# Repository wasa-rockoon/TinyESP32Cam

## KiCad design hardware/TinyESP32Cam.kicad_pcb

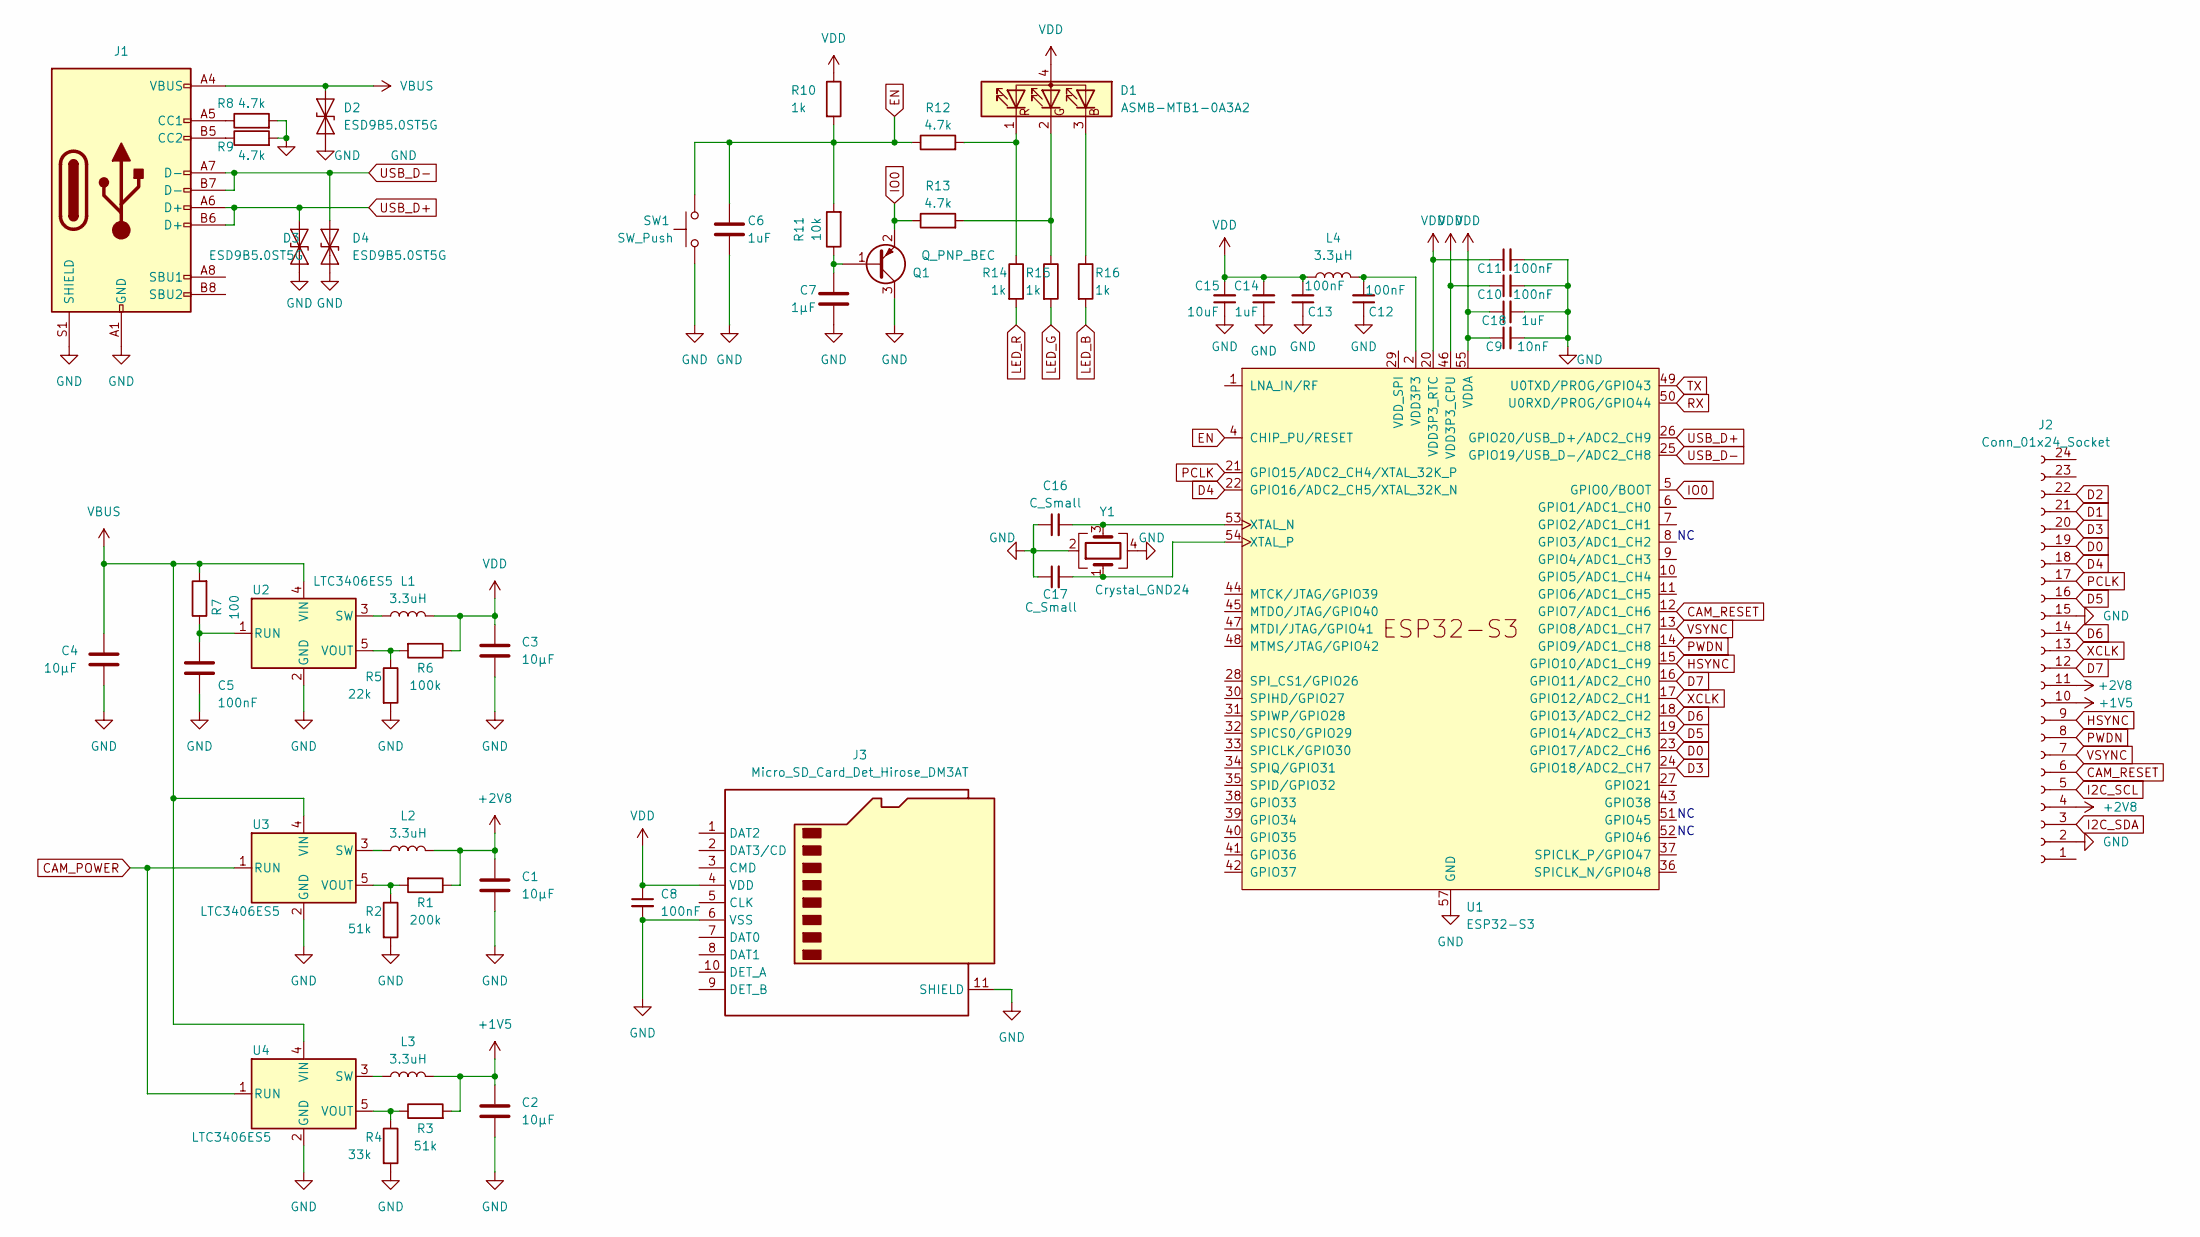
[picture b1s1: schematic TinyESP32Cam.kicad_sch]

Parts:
C1, C2, C3, C4: 10µF; C_0603_1608Metric
C5, C8, C10, C11, C12, C13: 100nF; C_0402_1005Metric
C6, C14, C18: 1uF; C_0402_1005Metric
C7: 1µF; C_0402_1005Metric
C9: 10nF; C_0402_1005Metric
C15: 10uF; C_0603_1608Metric
C16, C17: C_Small; C_0402_1005Metric
D1: ASMB-MTB1-0A3A2; LED_Cree-PLCC4_2x2mm_CW
D2, D3, D4: ESD9B5.0ST5G; D_SOD-523
J1: TYPE-C 16PFS 2JCB0.8-H7.45 IPX8; USB-C-SMD_SHOUHAN_TYPE-C-16PFS-2JCB0.8-H7.45
J2: Conn_01x24_Socket; Hirose_FH12-24S-0.5SH_1x24-1MP_P0.50mm_Horizontal
J3: Micro_SD_Card_Det_Hirose_DM3AT; microSD_HC_Hirose_DM3AT-SF-PEJM5
L1, L2, L3: 3.3uH; L_Murata_LQH2MCNxxxx02_2.0x1.6mm
L4: 3.3µH; L_Murata_LQH2MCNxxxx02_2.0x1.6mm
Q1: Q_PNP_BEC; SOT-23
R1: 200k; R_0402_1005Metric
R2, R3: 51k; R_0402_1005Metric
R4: 33k; R_0402_1005Metric
R5: 22k; R_0402_1005Metric
R6: 100k; R_0402_1005Metric
R7: 100; R_0402_1005Metric
R8, R9, R12, R13: 4.7k; R_0402_1005Metric
R10, R14, R15, R16: 1k; R_0402_1005Metric
R11: 10k; R_0402_1005Metric
SW1: SW_Push; SW_SPST_CK_KXT3
U1: ESP32-S3; QFN-56-1EP_7x7mm_P0.4mm_EP5.6x5.6mm
U2, U3, U4: LTC3406ES5; TSOT-23-5
Y1: Crystal_GND24; Crystal_SMD_2520-4Pin_2.5x2.0mm

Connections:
+1V5: C2.1, J2.10, L3.2, R3.2
+2V8: C1.1, J2.4, J2.11, L2.2, R1.1
CAM_POWER: U3.1 (RUN), U4.1 (RUN)
CAM_RESET: J2.6, U1.12 (GPIO7/ADC1_CH6)
D0: J2.19, U1.23 (GPIO17/ADC2_CH6)
D1: J2.21
D2: J2.22
D3: J2.20, U1.24 (GPIO18/ADC2_CH7)
D4: J2.18, U1.22 (GPIO16/ADC2_CH5/XTAL_32K_N)
D5: J2.16, U1.19 (GPIO14/ADC2_CH3)
D6: J2.14, U1.18 (GPIO13/ADC2_CH2)
D7: J2.12, U1.16 (GPIO11/ADC2_CH0)
EN: C6.1, R10.2, R11.2, R12.1, SW1.2, U1.4 (CHIP_PU/RESET)
GND: C1.2, C2.2, C3.2, C4.2, C5.2, C6.2, C7.2, C8.2, C9.2, C10.2, C11.2, C12.1, C13.1, C14.1, C15.1, C16.1, C17.1, C18.2, D2.1 (A1), D3.1 (A1), D4.1 (A1), J1.A1 (GND), J1.A12 (GND), J1.B1 (GND), J1.B12 (GND), J1.S1 (SHIELD), J2.2, J2.15, J3.6 (VSS), J3.11 (SHIELD), Q1.3 (C), R2.2, R4.2, R5.2, R8.2, R9.2, SW1.1, U1.57 (GND), U2.2 (GND), U3.2 (GND), U4.2 (GND), Y1.2, Y1.4
HSYNC: J2.9, U1.15 (GPIO10/ADC1_CH9)
I2C_SCL: J2.5
I2C_SDA: J2.3
IO0: Q1.2 (E), R13.1, U1.5 (GPIO0/BOOT)
LED_B: R16.2
LED_G: R15.2
LED_R: R14.2
unnamed: D1.3 (BK), R16.1
unnamed: D1.2 (GK), R13.2, R15.1
unnamed: D1.1 (RK), R12.2, R14.1
unnamed: J1.A5 (CC1), R8.1
unnamed: J1.B5 (CC2), R9.1
unnamed: C7.1, Q1.1 (B), R11.1
unnamed: C16.2, U1.53 (XTAL_N), Y1.3
unnamed: C17.2, U1.54 (XTAL_P), Y1.1
unnamed: C5.1, R7.1, U2.1 (RUN)
unnamed: L1.1, U2.3 (SW)
unnamed: R5.1, R6.2, U2.5 (VOUT)
unnamed: L2.1, U3.3 (SW)
unnamed: R1.2, R2.1, U3.5 (VOUT)
unnamed: L3.1, U4.3 (SW)
unnamed: R3.1, R4.1, U4.5 (VOUT)
PCLK: J2.17, U1.21 (GPIO15/ADC2_CH4/XTAL_32K_P)
PWDN: J2.8, U1.14 (GPIO9/ADC1_CH8)
RX: U1.50 (U0RXD/PROG/GPIO44)
TX: U1.49 (U0TXD/PROG/GPIO43)
USB_D+: D3.2 (A2), J1.A6 (D+), J1.B6 (D+), U1.26 (GPIO20/USB_D+/ADC2_CH9)
USB_D-: D4.2 (A2), J1.A7 (D-), J1.B7 (D-), U1.25 (GPIO19/USB_D-/ADC2_CH8)
VBUS: C4.1, D2.2 (A2), J1.A4 (VBUS), J1.A9 (VBUS), J1.B4 (VBUS), J1.B9 (VBUS), R7.2, U2.4 (VIN), U3.4 (VIN), U4.4 (VIN)
VDD: C3.1, C8.1, C9.1, C10.1, C11.1, C13.2, C14.2, C15.2, C18.1, D1.4 (A), J3.4 (VDD), L1.2, L4.1, R6.1, R10.1, U1.20 (VDD3P3_RTC), U1.46 (VDD3P3_CPU), U1.55 (VDDA), U1.56 (VDDA)
VDD3P3: C12.2, L4.2, U1.2 (VDD3P3), U1.3 (VDD3P3)
VSYNC: J2.7, U1.13 (GPIO8/ADC1_CH7)
XCLK: J2.13, U1.17 (GPIO12/ADC2_CH1)

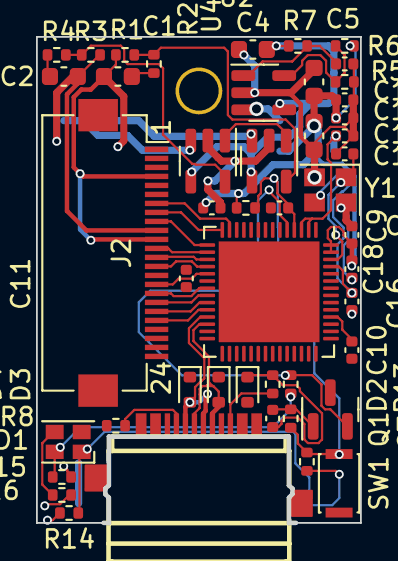
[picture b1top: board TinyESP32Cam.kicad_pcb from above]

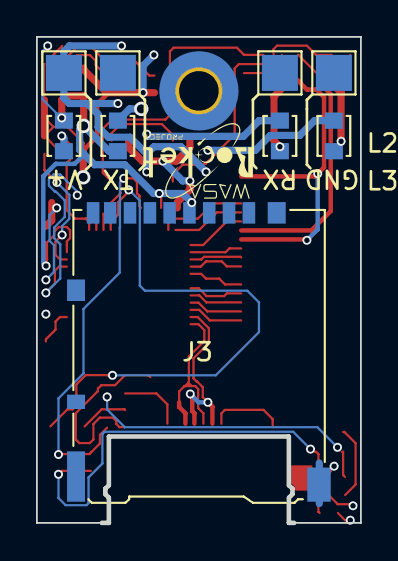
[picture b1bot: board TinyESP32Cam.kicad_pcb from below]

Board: 2 copper layers, 17.8 x 26.9 mm, 52 parts (5 on the bottom side), 38 nets.

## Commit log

2023-10-05 Side version
